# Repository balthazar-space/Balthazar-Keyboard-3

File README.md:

# Balthazar

Open-hardware laptop computer modules description and concept.

These are electronic schematic modules as presented at https://balthazar.space/wiki/Balthazar with the main aim for team access. See the [main repository](https://github.com/balthazar-space/balthazar) for other designs.

# Balthazar Keyboard 3

Balthazar keyboard with keycaps.

Computer Keyboard version 3 system built around an 8-bit Atmel ATmega 32u4 microcontroller. A normal ISO keyboard layout is used. The PCB design is for Cherry keycaps. Schematics layout and connections are a bit simplified over version 2.

An option is given for the onboard microcontroller to handle also the control for PSU board, the OLED module, bluetooth module and the ps/2 touchpad module. For this I2C, SPI and PS/2 serial connections are exposed - and are optional. The QMK code has not been updated with all these options yet. 

QMK code in QMK folder reflects the simplifications of this version - basically just the more straightforward selection of row pins of the microcontroller.

Keyboard pcb has dimensions predefined by the LCD's dimensions of 13.3 inch diagonal: 290mm width. The width is the most determining factor for the keys raster which is about 17mm – instead of the regular 19mm.

The keys have some ergonomic solution that gives some additional design touch. The keycaps here are positioned vertically which is not the best solution (keycaps orientation should follow the wave of the design...). 

KiCad 5.1.5 files are uploaded here as well as the drawings pictures and firmware code.

### OLED & boot sequence

A 128x32 SSD130 64x128 display connected via i2c is used.
When starting up, you are asked to enter a password. If it's not set up yet, a new one can be entered.
After successful authentication, a boot menu is presented.

**_beware:_** The password is saved plaintext in the microcontroller's EEPROM. It can be extracted with proper equipment and can easily be overwritten on the currently used ATmega32u4.

## License

All resources except the keyboard firmware - which is licensed with with GPLv3 or later - licensed under the CERN Open Hardware Licence CERN-OHL W V.2.0

Version 2.0 of the CERN-OHL introduces three variants of the licence – strongly (S) reciprocal, weakly (W) reciprocal and permissive (P) – which aim to address specific constraints caused by different collaboration models currently used in open-hardware projects. 

The first two variants mean that if any product is made using an open hardware design, the design of that product, including any improvements or modifications, should be made available under the same licence as that of the original product. Permissive licences do not impose this condition.

See the [LICENSE.md](./LICENSE.md) file for more information.

## Funding

This project is funded through the [NGI Zero Entrust Fund](https://nlnet.nl/entrust), a fund
established by [NLnet](https://nlnet.nl) with financial support from the European Commission's
[Next Generation Internet](https://ngi.eu) program. Learn more on the [NLnet project page](https://nlnet.nl/project/Balthazar-Casing/).

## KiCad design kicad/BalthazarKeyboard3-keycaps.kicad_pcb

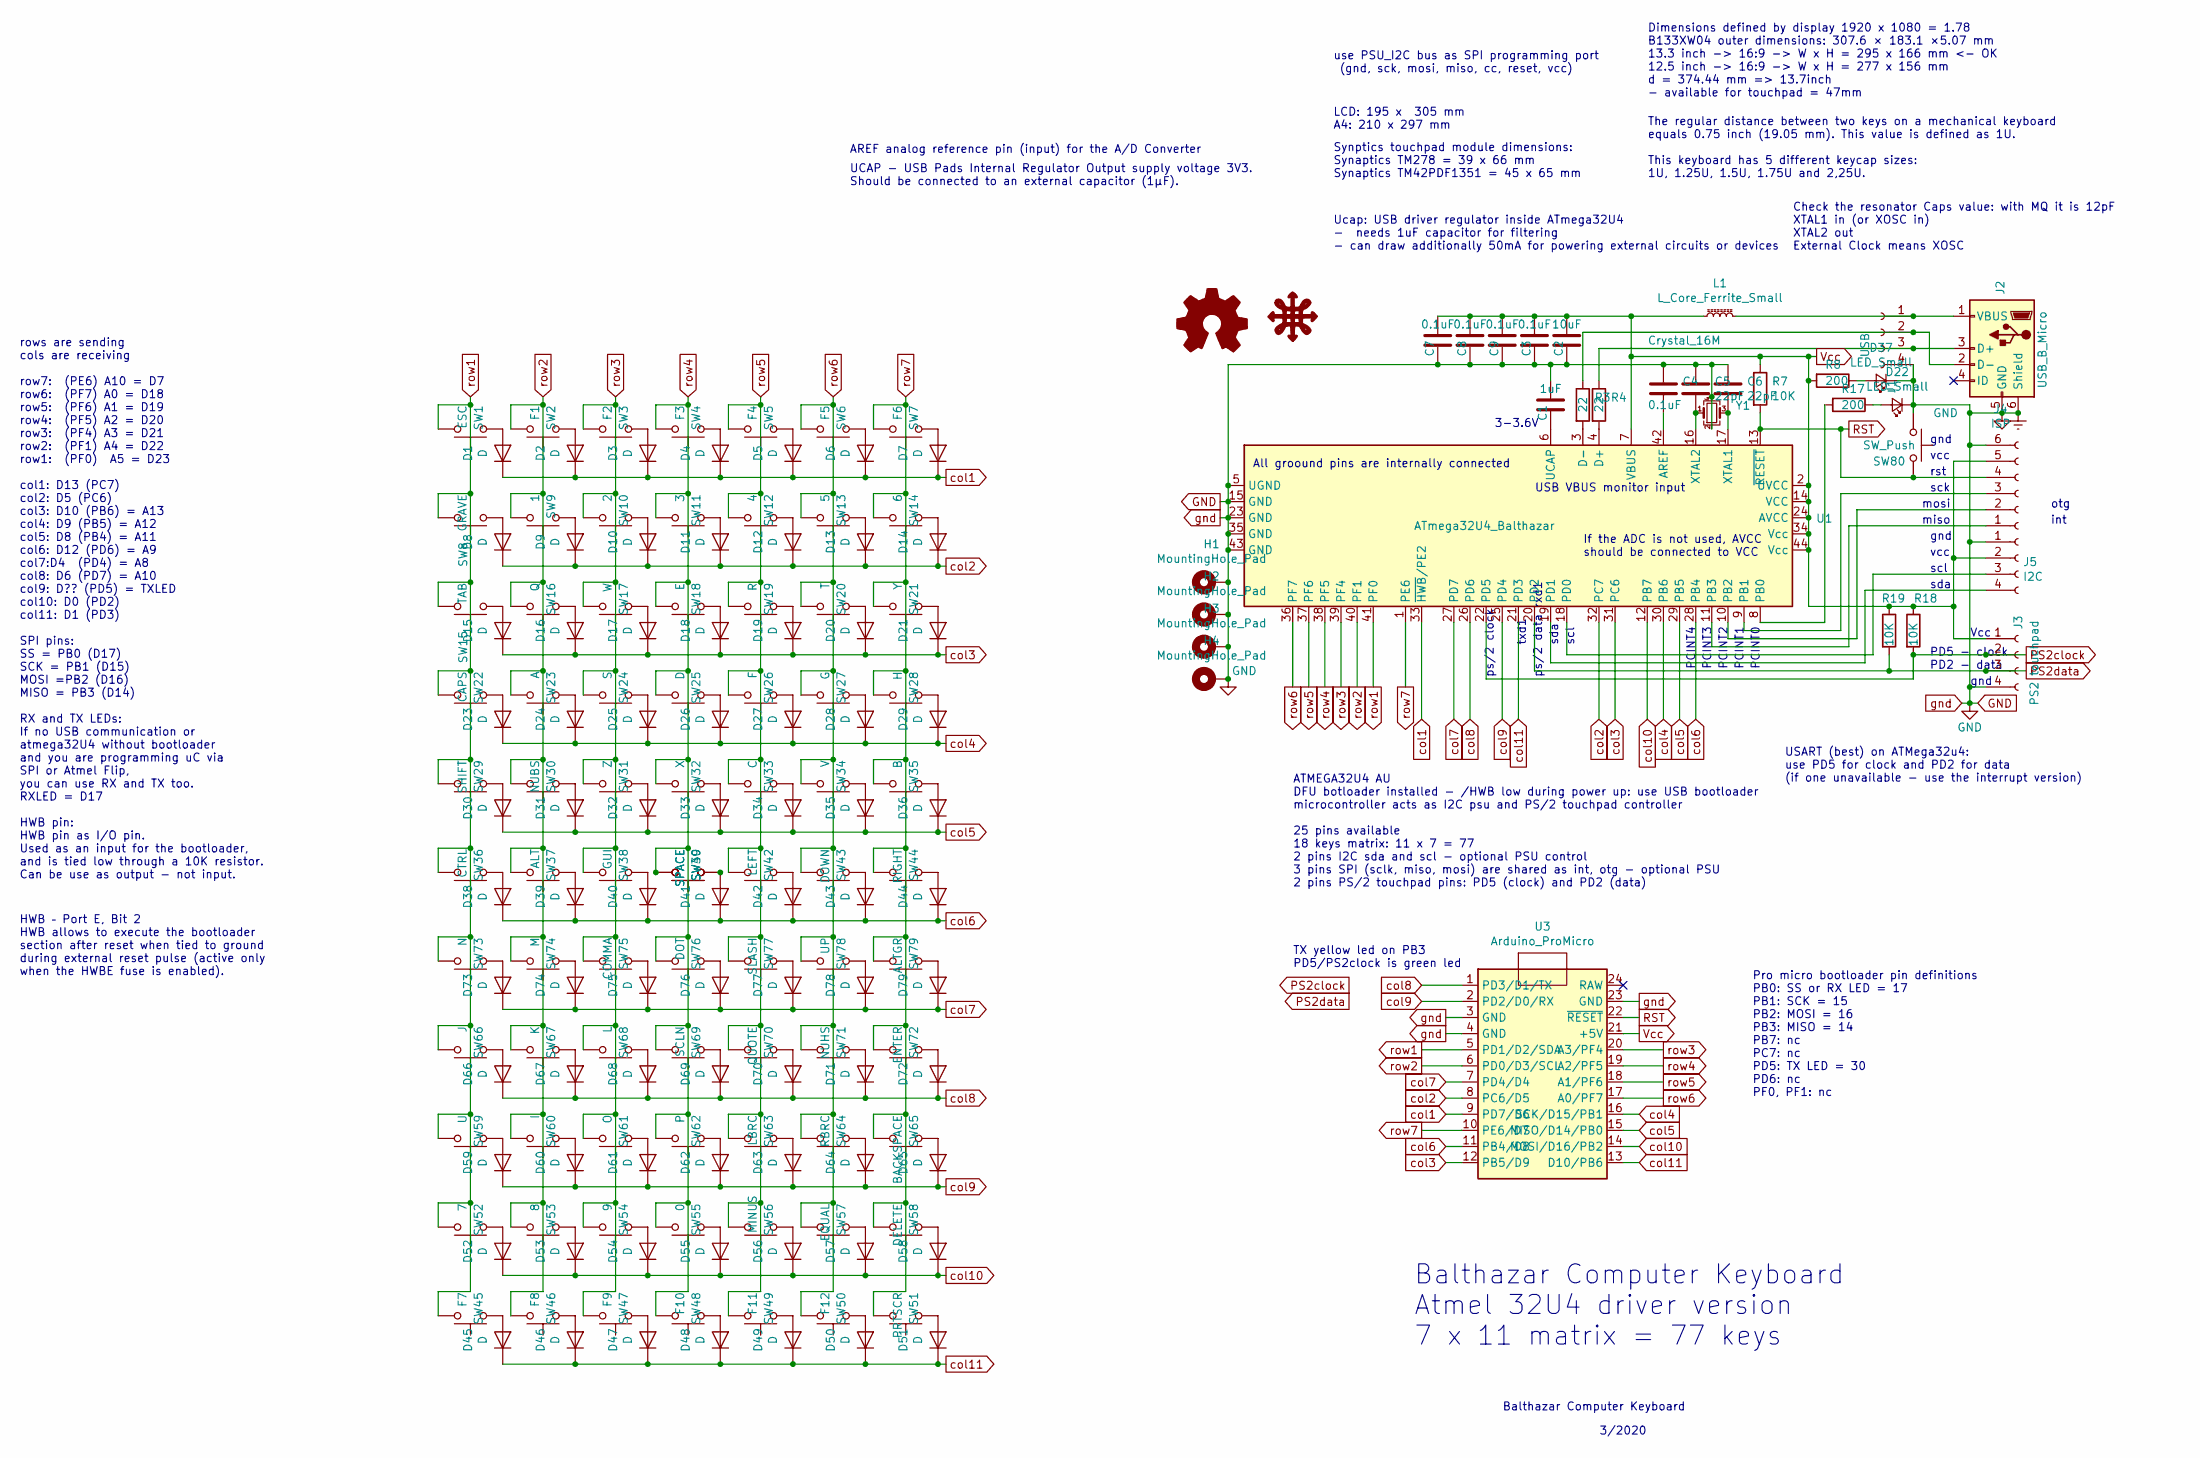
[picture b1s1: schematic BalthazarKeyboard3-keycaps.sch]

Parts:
C1: 1uF; C_1206_3216Metric
C2: 10uF; C_1206_3216Metric
C3, C4, C7, C8, C9: 0.1uF; C_1206_3216Metric
C5, C6: 22pF; C_0805_2012Metric
D1, D2, D3, D4, D5, D6, D7, D8, D9, D10, D11, D12, D13, D14, D15, D16, D17, D18, D19, D20, D21, D23, D24, D25, D26, D27, D28, D29, D30, D31, D32, D33, D34, D35, D36, D38, D39, D40, D41, D42, D43, D44, D45, D46, D47, D48, D49, D50, D51, D52, D53, D54, D55, D56, D57, D58, D59, D60, D61, D62, D63, D64, D65, D66, D67, D68, D69, D70, D71, D72, D73, D74, D75, D76, D77, D78, D79: D; D_1206_3216Metric
D22, D37: LED_Small; LED_1206_3216Metric
H1, H2, H3, H4: MountingHole_Pad; MountingHole_2.7mm_M2.5_DIN965_Pad
J1: USB; PinSocket_1x04_P2.00mm_Horizontal
J2: USB_B_Micro; USB_Micro-B_Molex-Balthazar
J3: PS2 touchpad; PinSocket_1x04_P2.00mm_Horizontal
J4: ISP; PinHeader_1x06_P2.00mm_Horizontal
J5: I2C; PinHeader_1x04_P2.54mm_Vertical
L1: L_Core_Ferrite_Small; D_1206_3216Metric
R3, R4: 22; R_1206_3216Metric
R7, R18, R19: 10K; R_1206_3216Metric
R8, R17: 200; R_1206_3216Metric
SW1: ESC; CherryMX_RGB_SpeedSilver
SW2: F1; CherryMX_RGB_SpeedSilver
SW3: F2; CherryMX_RGB_SpeedSilver
SW4: F3; CherryMX_RGB_SpeedSilver
SW5: F4; CherryMX_RGB_SpeedSilver
SW6: F5; CherryMX_RGB_SpeedSilver
SW7: F6; CherryMX_RGB_SpeedSilver
SW8: GRAVE; CherryMX_RGB_SpeedSilver
SW9: 1; CherryMX_RGB_SpeedSilver
SW10: 2; CherryMX_RGB_SpeedSilver
SW11: 3; CherryMX_RGB_SpeedSilver
SW12: 4; CherryMX_RGB_SpeedSilver
SW13: 5; CherryMX_RGB_SpeedSilver
SW14: 6; CherryMX_RGB_SpeedSilver
SW15: TAB; CherryMX_RGB_SpeedSilver
SW16: Q; CherryMX_RGB_SpeedSilver
SW17: W; CherryMX_RGB_SpeedSilver
SW18: E; CherryMX_RGB_SpeedSilver
SW19: R; CherryMX_RGB_SpeedSilver
SW20: T; CherryMX_RGB_SpeedSilver
SW21: Y; CherryMX_RGB_SpeedSilver
SW22: CAPS; CherryMX_RGB_SpeedSilver
SW23: A; CherryMX_RGB_SpeedSilver
SW24: S; CherryMX_RGB_SpeedSilver
SW25: D; CherryMX_RGB_SpeedSilver
SW26: F; CherryMX_RGB_SpeedSilver
SW27: G; CherryMX_RGB_SpeedSilver
SW28: H; CherryMX_RGB_SpeedSilver
SW29: SHIFT; CherryMX_RGB_SpeedSilver
SW30: NUBS; CherryMX_RGB_SpeedSilver
SW31: Z; CherryMX_RGB_SpeedSilver
SW32: X; CherryMX_RGB_SpeedSilver
SW33: C; CherryMX_RGB_SpeedSilver
SW34: V; CherryMX_RGB_SpeedSilver
SW35: B; CherryMX_RGB_SpeedSilver
SW36: CTRL; CherryMX_RGB_SpeedSilver
SW37: ALT; CherryMX_RGB_SpeedSilver
SW38: GUI; CherryMX_RGB_SpeedSilver
SW39, SW40: SPACE; CherryMX_RGB_SpeedSilver
SW42: LEFT; CherryMX_RGB_SpeedSilver
SW43: DOWN; CherryMX_RGB_SpeedSilver
SW44: RIGHT; CherryMX_RGB_SpeedSilver
SW45: F7; CherryMX_RGB_SpeedSilver
SW46: F8; CherryMX_RGB_SpeedSilver
SW47: F9; CherryMX_RGB_SpeedSilver
SW48: F10; CherryMX_RGB_SpeedSilver
SW49: F11; CherryMX_RGB_SpeedSilver
SW50: F12; CherryMX_RGB_SpeedSilver
SW51: PRTSCR; CherryMX_RGB_SpeedSilver
SW52: 7; CherryMX_RGB_SpeedSilver
SW53: 8; CherryMX_RGB_SpeedSilver
SW54: 9; CherryMX_RGB_SpeedSilver
SW55: 0; CherryMX_RGB_SpeedSilver
SW56: MINUS; CherryMX_RGB_SpeedSilver
SW57: EQUAL; CherryMX_RGB_SpeedSilver
SW58: DELETE; CherryMX_RGB_SpeedSilver
SW59: U; CherryMX_RGB_SpeedSilver
SW60: I; CherryMX_RGB_SpeedSilver
SW61: O; CherryMX_RGB_SpeedSilver
SW62: P; CherryMX_RGB_SpeedSilver
SW63: LBRC; CherryMX_RGB_SpeedSilver
SW64: RBRC; CherryMX_RGB_SpeedSilver
SW65: BACKSPACE; CherryMX_RGB_SpeedSilver
SW66: J; CherryMX_RGB_SpeedSilver
SW67: K; CherryMX_RGB_SpeedSilver
SW68: L; CherryMX_RGB_SpeedSilver
SW69: SCLN; CherryMX_RGB_SpeedSilver
SW70: QUOTE; CherryMX_RGB_SpeedSilver
SW71: NUHS; CherryMX_RGB_SpeedSilver
SW72: ENTER; CherryMX_RGB_SpeedSilver
SW73: N; CherryMX_RGB_SpeedSilver
SW74: M; CherryMX_RGB_SpeedSilver
SW75: COMMA; CherryMX_RGB_SpeedSilver
SW76: DOT; CherryMX_RGB_SpeedSilver
SW77: SLASH; CherryMX_RGB_SpeedSilver
SW78: UP; CherryMX_RGB_SpeedSilver
SW79: ALTGR; CherryMX_RGB_SpeedSilver
SW80: SW_Push; SW_SPST_CK_RS282G05A3
U1: ATmega32U4_Balthazar; TQFP-44_10x10mm_P0.8mm
U3: Arduino_ProMicro
Y1: Crystal_16M; Crystal_SMD_SeikoEpson_MC306-4Pin_8.0x3.2mm_HandSoldering

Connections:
GND: C1.2, C2.1, C3.1, C4.2, C5.2, C6.2, C7.1, C8.1, C9.1, D22.1 (K), D37.1 (K), H1.1, H2.1, H3.1, H4.1, J1.4, J2.5 (GND), J2.6 (Shield), J3.4, J4.6, J5.1, SW80.1, U1.5 (UGND), U1.15 (GND), U1.23 (GND), U1.35 (GND), U1.43 (GND), U3.3 (GND), U3.4 (GND), U3.23 (GND), Y1.2, Y1.4; also elsewhere on the board
unnamed: C1.1, U1.6 (UCAP)
unnamed: C4.1, U1.42 (AREF)
unnamed: C5.1, U1.16 (XTAL2), Y1.1
unnamed: C6.1, U1.17 (XTAL1), Y1.3
unnamed: D1.2 (A), SW1.2
unnamed: D2.2 (A), SW2.2
unnamed: D3.2 (A), SW3.2
unnamed: D4.2 (A), SW4.2
unnamed: D5.2 (A), SW5.2
unnamed: D6.2 (A), SW6.2
unnamed: D7.2 (A), SW7.2
unnamed: D8.2 (A), SW8.2
unnamed: D9.2 (A), SW9.2
unnamed: D10.2 (A), SW10.2
unnamed: D11.2 (A), SW11.2
unnamed: D12.2 (A), SW12.2
unnamed: D13.2 (A), SW13.2
unnamed: D14.2 (A), SW14.2
unnamed: D15.2 (A), SW15.2
unnamed: D16.2 (A), SW16.2
unnamed: D17.2 (A), SW17.2
unnamed: D18.2 (A), SW18.2
unnamed: D19.2 (A), SW19.2
unnamed: D20.2 (A), SW20.2
unnamed: D21.2 (A), SW21.2
unnamed: D22.2 (A), R17.1
unnamed: D23.2 (A), SW22.2
unnamed: D24.2 (A), SW23.2
unnamed: D25.2 (A), SW24.2
unnamed: D26.2 (A), SW25.2
unnamed: D27.2 (A), SW26.2
unnamed: D28.2 (A), SW27.2
unnamed: D29.2 (A), SW28.2
unnamed: D30.2 (A), SW29.2
unnamed: D31.2 (A), SW30.2
unnamed: D32.2 (A), SW31.2
unnamed: D33.2 (A), SW32.2
unnamed: D34.2 (A), SW33.2
unnamed: D35.2 (A), SW34.2
unnamed: D36.2 (A), SW35.2
unnamed: D37.2 (A), R8.1
unnamed: D38.2 (A), SW36.2
unnamed: D39.2 (A), SW37.2
unnamed: D40.2 (A), SW38.2
unnamed: D41.2 (A), SW39.2, SW40.2
unnamed: D42.2 (A), SW42.2
unnamed: D43.2 (A), SW43.2
unnamed: D44.2 (A), SW44.2
unnamed: D45.2 (A), SW45.2
unnamed: D46.2 (A), SW46.2
unnamed: D47.2 (A), SW47.2
unnamed: D48.2 (A), SW48.2
unnamed: D49.2 (A), SW49.2
unnamed: D50.2 (A), SW50.2
unnamed: D51.2 (A), SW51.2
unnamed: D52.2 (A), SW52.2
unnamed: D53.2 (A), SW53.2
unnamed: D54.2 (A), SW54.2
unnamed: D55.2 (A), SW55.2
unnamed: D56.2 (A), SW56.2
unnamed: D57.2 (A), SW57.2
unnamed: D58.2 (A), SW58.2
unnamed: D59.2 (A), SW59.2
unnamed: D60.2 (A), SW60.2
unnamed: D61.2 (A), SW61.2
unnamed: D62.2 (A), SW62.2
unnamed: D63.2 (A), SW63.2
unnamed: D64.2 (A), SW64.2
unnamed: D65.2 (A), SW65.2
unnamed: D66.2 (A), SW66.2
unnamed: D67.2 (A), SW67.2
unnamed: D68.2 (A), SW68.2
unnamed: D69.2 (A), SW69.2
unnamed: D70.2 (A), SW70.2
unnamed: D71.2 (A), SW71.2
unnamed: D72.2 (A), SW72.2
unnamed: D73.2 (A), SW73.2
unnamed: D74.2 (A), SW74.2
unnamed: D75.2 (A), SW75.2
unnamed: D76.2 (A), SW76.2
unnamed: D77.2 (A), SW77.2
unnamed: D78.2 (A), SW78.2
unnamed: D79.2 (A), SW79.2
unnamed: J1.1, J2.1 (VBUS), L1.2
unnamed: J1.2, J2.2 (D-), R3.1
unnamed: J1.3, J2.3 (D+), R4.1
unnamed: J4.1, U1.11 (PB3)
unnamed: J4.2, U1.10 (PB2)
unnamed: J4.3, U1.9 (PB1)
unnamed: J5.3, U1.18 (PD0)
unnamed: J5.4, U1.19 (PD1)
unnamed: R3.2, U1.3 (D-)
unnamed: R4.2, U1.4 (D+)
unnamed: R17.2, U1.8 (PB0)
PS2clock: J3.2, R18.2, U1.22 (PD5)
PS2data: J3.3, R19.2, U1.20 (PD2)
RST: J4.4, R7.2, SW80.2, U1.13 (~RESET), U3.22 (~RESET)
Vcc: C2.2, C3.2, C7.2, C8.2, C9.2, J3.1, J4.5, J5.2, L1.1, R7.1, R8.2, R18.1, R19.1, U1.2 (UVCC), U1.7 (VBUS), U1.14 (VCC), U1.24 (AVCC), U1.34 (Vcc), U1.44 (Vcc), U3.21 (+5V)
col1: D1.1 (K), D2.1 (K), D3.1 (K), D4.1 (K), D5.1 (K), D6.1 (K), D7.1 (K), U1.33 (~HWB~/PE2), U3.9 (PD7/D6)
col2: D8.1 (K), D9.1 (K), D10.1 (K), D11.1 (K), D12.1 (K), D13.1 (K), D14.1 (K), U1.32 (PC7), U3.8 (PC6/D5)
col3: D15.1 (K), D16.1 (K), D17.1 (K), D18.1 (K), D19.1 (K), D20.1 (K), D21.1 (K), U1.31 (PC6), U3.12 (PB5/D9)
col4: D23.1 (K), D24.1 (K), D25.1 (K), D26.1 (K), D27.1 (K), D28.1 (K), D29.1 (K), U1.30 (PB6), U3.16 (SCK/D15/PB1)
col5: D30.1 (K), D31.1 (K), D32.1 (K), D33.1 (K), D34.1 (K), D35.1 (K), D36.1 (K), U1.29 (PB5), U3.15 (MISO/D14/PB0)
col6: D38.1 (K), D39.1 (K), D40.1 (K), D41.1 (K), D42.1 (K), D43.1 (K), D44.1 (K), U1.28 (PB4), U3.11 (PB4/D8)
col7: D73.1 (K), D74.1 (K), D75.1 (K), D76.1 (K), D77.1 (K), D78.1 (K), D79.1 (K), U1.27 (PD7), U3.7 (PD4/D4)
col8: D66.1 (K), D67.1 (K), D68.1 (K), D69.1 (K), D70.1 (K), D71.1 (K), D72.1 (K), U1.26 (PD6), U3.1 (PD3/D1/TX)
col9: D59.1 (K), D60.1 (K), D61.1 (K), D62.1 (K), D63.1 (K), D64.1 (K), D65.1 (K), U1.25 (PD4), U3.2 (PD2/D0/RX)
col10: D52.1 (K), D53.1 (K), D54.1 (K), D55.1 (K), D56.1 (K), D57.1 (K), D58.1 (K), U1.12 (PB7), U3.14 (MOSI/D16/PB2)
col11: D45.1 (K), D46.1 (K), D47.1 (K), D48.1 (K), D49.1 (K), D50.1 (K), D51.1 (K), U1.21 (PD3), U3.13 (D10/PB6)
row1: SW1.1, SW8.1, SW15.1, SW22.1, SW29.1, SW36.1, SW45.1, SW52.1, SW59.1, SW66.1, SW73.1, U1.41 (PF0), U3.5 (PD1/D2/SDA)
row2: SW2.1, SW9.1, SW16.1, SW23.1, SW30.1, SW37.1, SW46.1, SW53.1, SW60.1, SW67.1, SW74.1, U1.40 (PF1), U3.6 (PD0/D3/SCL)
row3: SW3.1, SW10.1, SW17.1, SW24.1, SW31.1, SW38.1, SW47.1, SW54.1, SW61.1, SW68.1, SW75.1, U1.39 (PF4), U3.20 (A3/PF4)
row4: SW4.1, SW11.1, SW18.1, SW25.1, SW32.1, SW39.1, SW40.1, SW48.1, SW55.1, SW62.1, SW69.1, SW76.1, U1.38 (PF5), U3.19 (A2/PF5)
row5: SW5.1, SW12.1, SW19.1, SW26.1, SW33.1, SW42.1, SW49.1, SW56.1, SW63.1, SW70.1, SW77.1, U1.37 (PF6), U3.18 (A1/PF6)
row6: SW6.1, SW13.1, SW20.1, SW27.1, SW34.1, SW43.1, SW50.1, SW57.1, SW64.1, SW71.1, SW78.1, U1.36 (PF7), U3.17 (A0/PF7)
row7: SW7.1, SW14.1, SW21.1, SW28.1, SW35.1, SW44.1, SW51.1, SW58.1, SW65.1, SW72.1, SW79.1, U1.1 (PE6), U3.10 (PE6/D7)

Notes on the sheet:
ATMEGA32U4 AU DFU botloader installed - /HWB low during power up: use USB bootloader microcontroller acts as I2C psu and PS/2 touchpad controller 25 pins available 18 keys matrix: 11 x 7 = 77 2 pins I2C sda and scl - optional PSU control 3 pins SPI (sclk, miso, mosi) are shared as int, otg - option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
Balthazar Computer Keyboard Atmel 32U4 driver version 7 x 11 matrix = 77 keys
Dimensions defined by display 1920 x 1080 = 1.78 B133XW04 outer dimensions: 307.6 × 183.1 ×5.07 mm 13.3 inch -> 16:9 -> W x H = 295 x 166 mm <- OK 12.5 inch -> 16:9 -> W x H = 277 x 156 mm d = 374.44 mm => 13.7inch - available for touchpad = 47mm
Synptics touchpad module dimensions: Synaptics TM278 = 39 x 66 mm Synaptics TM42PDF1351 = 45 x 65 mm
The regular distance between two keys on a mechanical keyboard equals 0.75 inch (19.05 mm). This value is defined as 1U. This keyboard has 5 different keycap sizes: 1U, 1.25U, 1.5U, 1.75U and 2,25U.
3/2020
Balthazar Computer Keyboard
Pro micro bootloader pin definitions PB0: SS or RX LED = 17 PB1: SCK = 15 PB2: MOSI = 16 PB3: MISO = 14 PB7: nc PC7: nc PD5: TX LED = 30 PD6: nc PF0, PF1: nc
rows are sending cols are receiving row7: (PE6) A10 = D7 row6: (PF7) A0 = D18 row5: (PF6) A1 = D19 row4: (PF5) A2 = D20 row3: (PF4) A3 = D21 row2: (PF1) A4 = D22 row1: (PF0) A5 = D23 col1: D13 (PC7) col2: D5 (PC6) col3: D10 (PB6) = A13 col4: D9 (PB5) = A12 col5: D8 (PB4) = A11 col6: D12 (PD6) = A9 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
use PSU_I2C bus as SPI programming port (gnd, sck, mosi, miso, cc, reset, vcc)
HWB – Port E, Bit 2 HWB allows to execute the bootloader section after reset when tied to ground during external reset pulse (active only when the HWBE fuse is enabled).
LCD: 195 x 305 mm A4: 210 x 297 mm
UCAP - USB Pads Internal Regulator Output supply voltage 3V3. Should be connected to an external capacitor (1μF).
AREF analog reference pin (input) for the A/D Converter
PD5 - clock PD2 - data
USART (best) on ATMega32u4: use PD5 for clock and PD2 for data (if one unavailable - use the interrupt version)
sck
mosi
miso
rst
USB VBUS monitor input
If the ADC is not used, AVCC should be connected to VCC
gnd
Vcc
otg
int
PCINT3
PCINT2
PCINT1
PCINT0
PCINT4
scl
sda
ps/2 data rxd1
txd1
ps/2 clock
Ucap: USB driver regulator inside ATmega32U4 - needs 1uF capacitor for filtering - can draw additionally 50mA for powering external circuits or devices
Check the resonator Caps value: with MQ it is 12pF XTAL1 in (or XOSC in) XTAL2 out External Clock means XOSC
3-3.6V
TX yellow led on PB3 PD5/PS2clock is green led

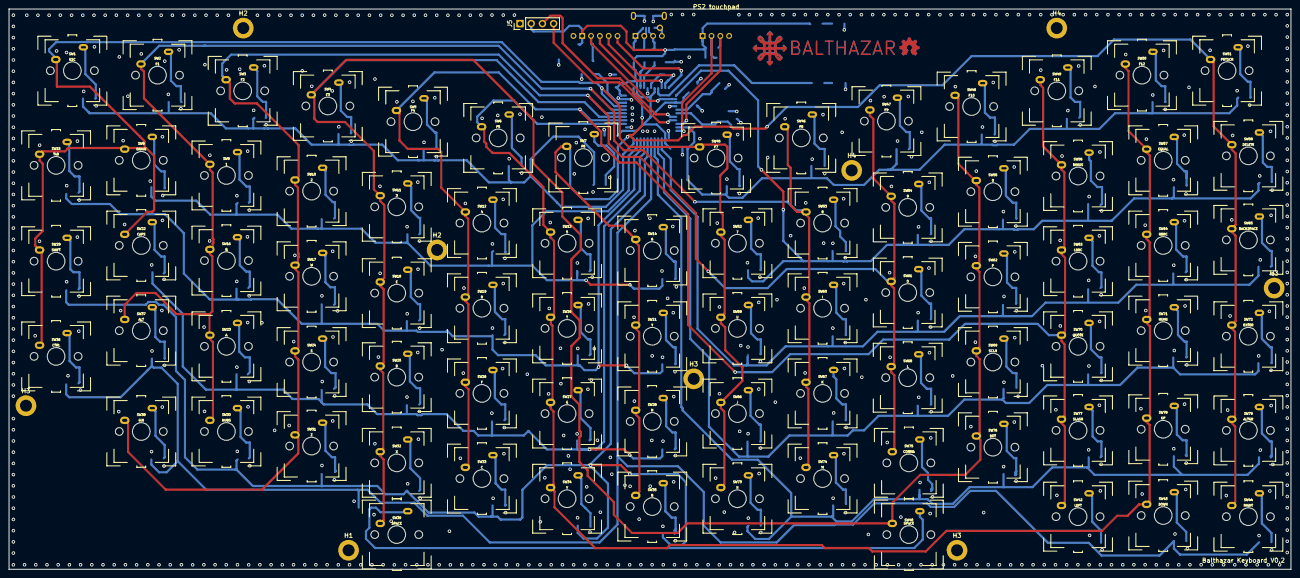
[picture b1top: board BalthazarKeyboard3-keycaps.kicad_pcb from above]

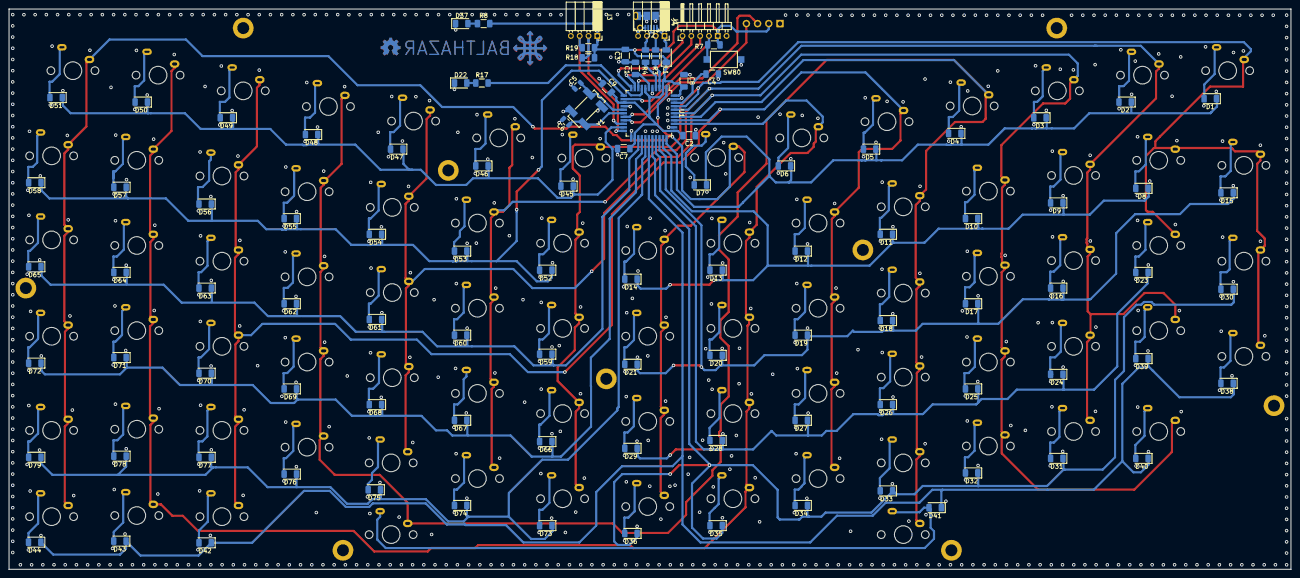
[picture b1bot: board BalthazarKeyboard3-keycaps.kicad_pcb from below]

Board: 4 copper layers, 290.6 x 127.0 mm, 191 parts (103 on the bottom side), 117 nets.

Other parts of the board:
H2#2, H3#2, H3#3, H3#4, H4#2: MountingHole_Pad; MountingHole_2.7mm_M2.5_DIN965_Pad

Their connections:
GND: H2#2.1, H3#2.1, H3#3.1, H3#4.1, H4#2.1; also elsewhere on the board

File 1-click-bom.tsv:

References,Qty,Description,Manufacturer,MPN,Manufacturer,MPN,Manufacturer,MPN,Manufacturer,MPN,Manufacturer,MPN,Digikey,Mouser,RS,Newark,Farnell,LCSC,JLC Assembly
C1,1,Multilayer Ceramic Capacitors MLCC - SMD/SMT WCAP-CSGP 1uF 1206 10% 16V MLCC,Wurth Elektronik,885012208036,AVX,885012208036,,TAJA105K035RNJ,,,,,732-7692-6-ND,581TAJA105K035R,1360144,,1135061,,
C2,1,Multilayer Ceramic Capacitors MLCC - SMD/SMT 25 VDC 10uF X5R 1206,KEMET,C1206C106M3PAC7210,,C1206C106M3PAC7210,,,,,,,,80C1206C106M3PACLR,,,3511493,,
"C5, C6",2,Multilayer Ceramic Capacitors MLCC - SMD/SMT 16V 22pF C0G 0805 5%,KYOCERA AVX,885012007012,Wurth Elektronik,885012007012,,,,,,,732-7816-1-ND,710885012007012,1814089,,2812134,,
"D1, D2, D3, D4, D5, D6, D7, D8, D9, D10, D11, D12, D13, D14, D15, D16, D17, D18, D19, D20, D21, D23, D24, D25, D26, D27, D28, D29, D30, D31, D32, D33, D34, D35, D36, D38, D39, D40, D41, D42, D43, D44, D45, D46, D47, D48, D49, D50, D51, D52, D53, D54, D55, D56, D57, D58, D59, D60, D61, D62, D63, D64, D65, D66, D67, D68, D69, D70, D71, D72, D73, D74, D75, D76, D77, D78, D79",77,"Diodes - General Purpose, Power, Switching 75V, 0.15A, Switching Diode & Array",Taiwan Semiconductor,TS4148 RXG,,TS4148 RXG,,,,,,,,821TS4148RXG,6526003,,2708388,,
"C3, C4, C7, C8, C9",5,Multilayer Ceramic Capacitors MLCC - SMD/SMT 50V 0.1uF X7R 1206 20%,KEMET,C1206C104M5RACTU,,C1206C104M5RACTU,,,,,,,399-C1206C104M5RAC7800DKR-ND,80C1206C104M5R,2053277P,,2581103,,",,,,,,,,,,,,,,,,,,,,,,,,,,,,,,,,,,,,,,,,,,,,,,,,,,,,,,,,,,,,,,,,,,,,,,,,,,,,"
"R7, R18, R19",3,Thick Film Resistors - SMD 10 kOhms 250 mW 1206 5%,Vishay,RC1206JR-0710KL,Panasonic,CRCW120610K0FKEA,Yageo,ERJ-8ENF1002V,Yageo,RC1206FR-0710KL,,RC1206JR-0710KL,311-10.0KFRCT-ND,603RC1206FR0710KL,1995772P,,9241000,,
"R3, R4",2,Thick Film Resistors - SMD 22ohms 1% 100ppm,Vishay Dale,RCC120622R0FKEA,,RCC120622R0FKEA,,,,,,,541-RCC120622R0FKEADKR-ND,71RCC120622R0FKEA,,,3755550,,
"R8, R17",2,Thick Film Resistors - SMD 200 Ohms 250 mW 1206 1%,Yageo,RC1206FR-07200RL,,RC1206FR-07200RL,,,,,,,311-200FRDKR-ND,603RC1206FR07200RL,,,3496175,,
L1,1,Fixed Inductors 1.5uH 10%,Cooper Bussmann,ILSB1206ER1R5K,Vishay Dale,MFBW1V3216-500-R,,ILSB1206ER1R5K,,,,,ILSB1206ER1R5K-ND,704MFBW1V3216500R,,,,,
U1,1,8-bit Microcontrollers - MCU USB 32K Flash 16 MHz,Microchip,ATMEGA32U4-AUR,,ATMEGA32U4-AUR,,,,,,,,,1772992P,,,,
Y1,1,Standard Clock Oscillators SG-8018CB 16.0000M-TJHPA3: MHZ OSC 1.8V~3.3V +/-50PPM -40~105C O/E 250TR,Epson,SG-8018CB 16.0000M-TJHPA3,,SG-8018CB 16.0000M-TJHPA3,,,,,,,,732CB16MTJHPA3,,,,,
"D22, D37",2,Standard LEDs - SMD Green,Stanley Electric,RPG1102W-660-TR,,RPG1102W-660-TR,,,,,,,404-1232-1-ND,327RPG1102W660TR,,,,,
SW1-SW79,78,"Pushbutton Switches Silver stem, RGB",Cherry,MX1A-51NA,,MX1A-51NA,,,,,,,MX1A-51NA-ND,,,,,,
SW80,1,Tactile Switches SPST 0.05A 12V 250gf,C&K Components,RS282G05A3SMRT,,RS282G05A3SMRT,,,,,,,CKN10384CT-ND,611RS282G05A3SMRT,1769434,,,,
J2,1,"USB Connectors Micro B Skt, Top Mount-SMT",Global Connector Technology,USB3505-30-A,,USB3505-30-A,,,,,,,,640USB350530A,,,,,

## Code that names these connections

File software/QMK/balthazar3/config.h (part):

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
// ROW pins are input pulled-up high pins; they are read according to the selected COL
#define MATRIX_ROW_PINS { F0, F1, F4, F5, F6, F7, E6 } 
// port F is problematic? Port F4,F5,F7 are also for JTAG testing interface - PF7 on one board not ok
// JTAG-capable MCUs come from the factory with the JTAGEN fuse set, and it takes over certain pins of the MCU that the board may be using for the switch matrix, LEDs, etc. - hfuse 0x99 (JTAG enabled) or 0xD9 (JTAG disabled)
// By default, with QMK the JTAG debugging interface is disabled as soon as the keyboard starts up. 
// defined in tmk_core/common/keyboard.c as function disable_jtag
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
/**
INT6/AIN0 – Port E, Bit 6
INT6, External Interrupt source 6: The PE6 pin can serve as an external interrupt source.
AIN0 – Analog Comparator Negative input. This pin is directly connected to the negative input of the Analog
Comparator.
• HWB – Port E, Bit 2
HWB allows to execute the bootloader section after reset when tied to ground during external reset pulse. The
HWB mode of this pin is active only when the HWBE fuse is enable. During normal operation (excluded Reset),
this pin acts as a general purpose I/O.
Overriding Signals for Alternate Functions PE6, PE2
Signal Name PE6/INT6/AIN0     PE2/HWB
PUOE          0                   0
PUOV          0                   0
DDOE          0                   0
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// pins unused by the keyboard for reference
#define UNUSED_PINS {}
//#define UNUSED_PINS  { E2, B0 }
// HWB/PE2 pin to ground - can be set as input only - never as output!

// Debounce reduces chatter (unintended double-presses) - default: 5; set 0 if debouncing is not needed
#define DEBOUNCE 5 //5
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//#define DEBUG_MATRIX_SCAN_RATE   // we get 1200 Hz to 500 Hz

/* 
 PB0 ISP ss - slave (SPI communication not used)  
 PB1 ISP sclk  
 PB2 ISP mosi  
 PB3 ISP miso	
 
 now PS/2:
 PB1 ps/2 clock PCINT1
 PB7 ps/2 data
*/

																																		
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
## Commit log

2022-01-21 Add files via upload
    KiCAD 5 files for a version of Balthazar keyboard PCB with keycaps. Also a little bit simplified usage of microcontroller pins. This is reflected in QMK scripts - will be added soon.
2022-01-26 Create License
2022-06-08 Adding interactive BOM
2022-06-28 Sorting files
2022-06-28 Moving backups to kicad directory
2022-06-28 kitspace.yaml
2022-06-28 Adding initial 1-click bom
2022-07-10 Parts update
2022-07-17 New build hex that works
2022-07-17 fixing include
2022-10-03 Rotating all keys, rerouting PCB - fix #4
2022-10-03 Adding 2 leyer production files
2022-10-03 Switching board to 4 layers
2022-10-03 Adding fidutials, adding pin descriptions
2022-10-03 Cache update
2022-10-03 Adding 4-layer production files
2024-06-25 Readme update
2024-06-25 Update readme, add license to firmware
2024-06-26 Update readme, add OLED support, logo, WIP boot sequence, new QMK fixes
2024-06-26 Add QMK firmware as submodule
2024-06-27 Bump QMK firmware version
2024-07-02 Reference latest QMK firmware

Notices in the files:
software/QMK/balthazar3/config.h:
This program is free software: you can redistribute it and/or modify
it under the terms of the GNU General Public License as published by
the Free Software Foundation, either version 2 of the License, or
(at your option) any later version.
